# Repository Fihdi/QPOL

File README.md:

# 8hp Quad Pole Phaser

QPOL is an 8hp Eurorack phaser module with four voltage controllable all pass filters. A variety of frequency responses can be achieved by mixing the phase shifted output back to the input signal. Chaining multiple phaser modules together allows for phasing with 4, 8, 12, 16 etc poles.

# IN
Connect an audio signal to the **IN** jack. The input signal is internally mixed together to the output of the **FDBK** section. This mixed signal is then fed to the four all pass filters. The **IN** signal is also routed to the **OUT** jack where it is mixed together the filter output **P4** with variable strength.
# SHIFT
The **SHIFT** knob, **CV** jack, as well as its attenuverter knob, set the the cutoff frequency of the all pass filters. By modulating the **SHIFT** parameter, the filter changes the phase shift of the **IN**. An LED indicates the level of modulation.
# FDBK
The FDBK attenuverter controls the amount and polarity of feedback from the filter output **P4**, which is added back to the input signal. An external signal from the **EXT** input jack can be routed to the FDBK attenuverter with the **P4 EXT** switch.
# P4, OUT and MIX

The **P4** jack directly outputs the fourth stage of the all pass filter core. When chaining multiple modules together to allow for more than four stages of phasing, this output can be used

The **MIX** knob sums the **IN** signal to the filter output **P4** with variable strength. By changing the Jumper on the back of the module from "Direct" to "Mixed" a different input signal is fed to the MIX section. The jumper being in the "Direct" position routes the signal from the **IN** jack to the MIX section as it is. In the "Direct" position, the summed signal of the **IN** jack and the **FDBK** output is fed to the MIX section.

The final output is available at the **OUT** jack.

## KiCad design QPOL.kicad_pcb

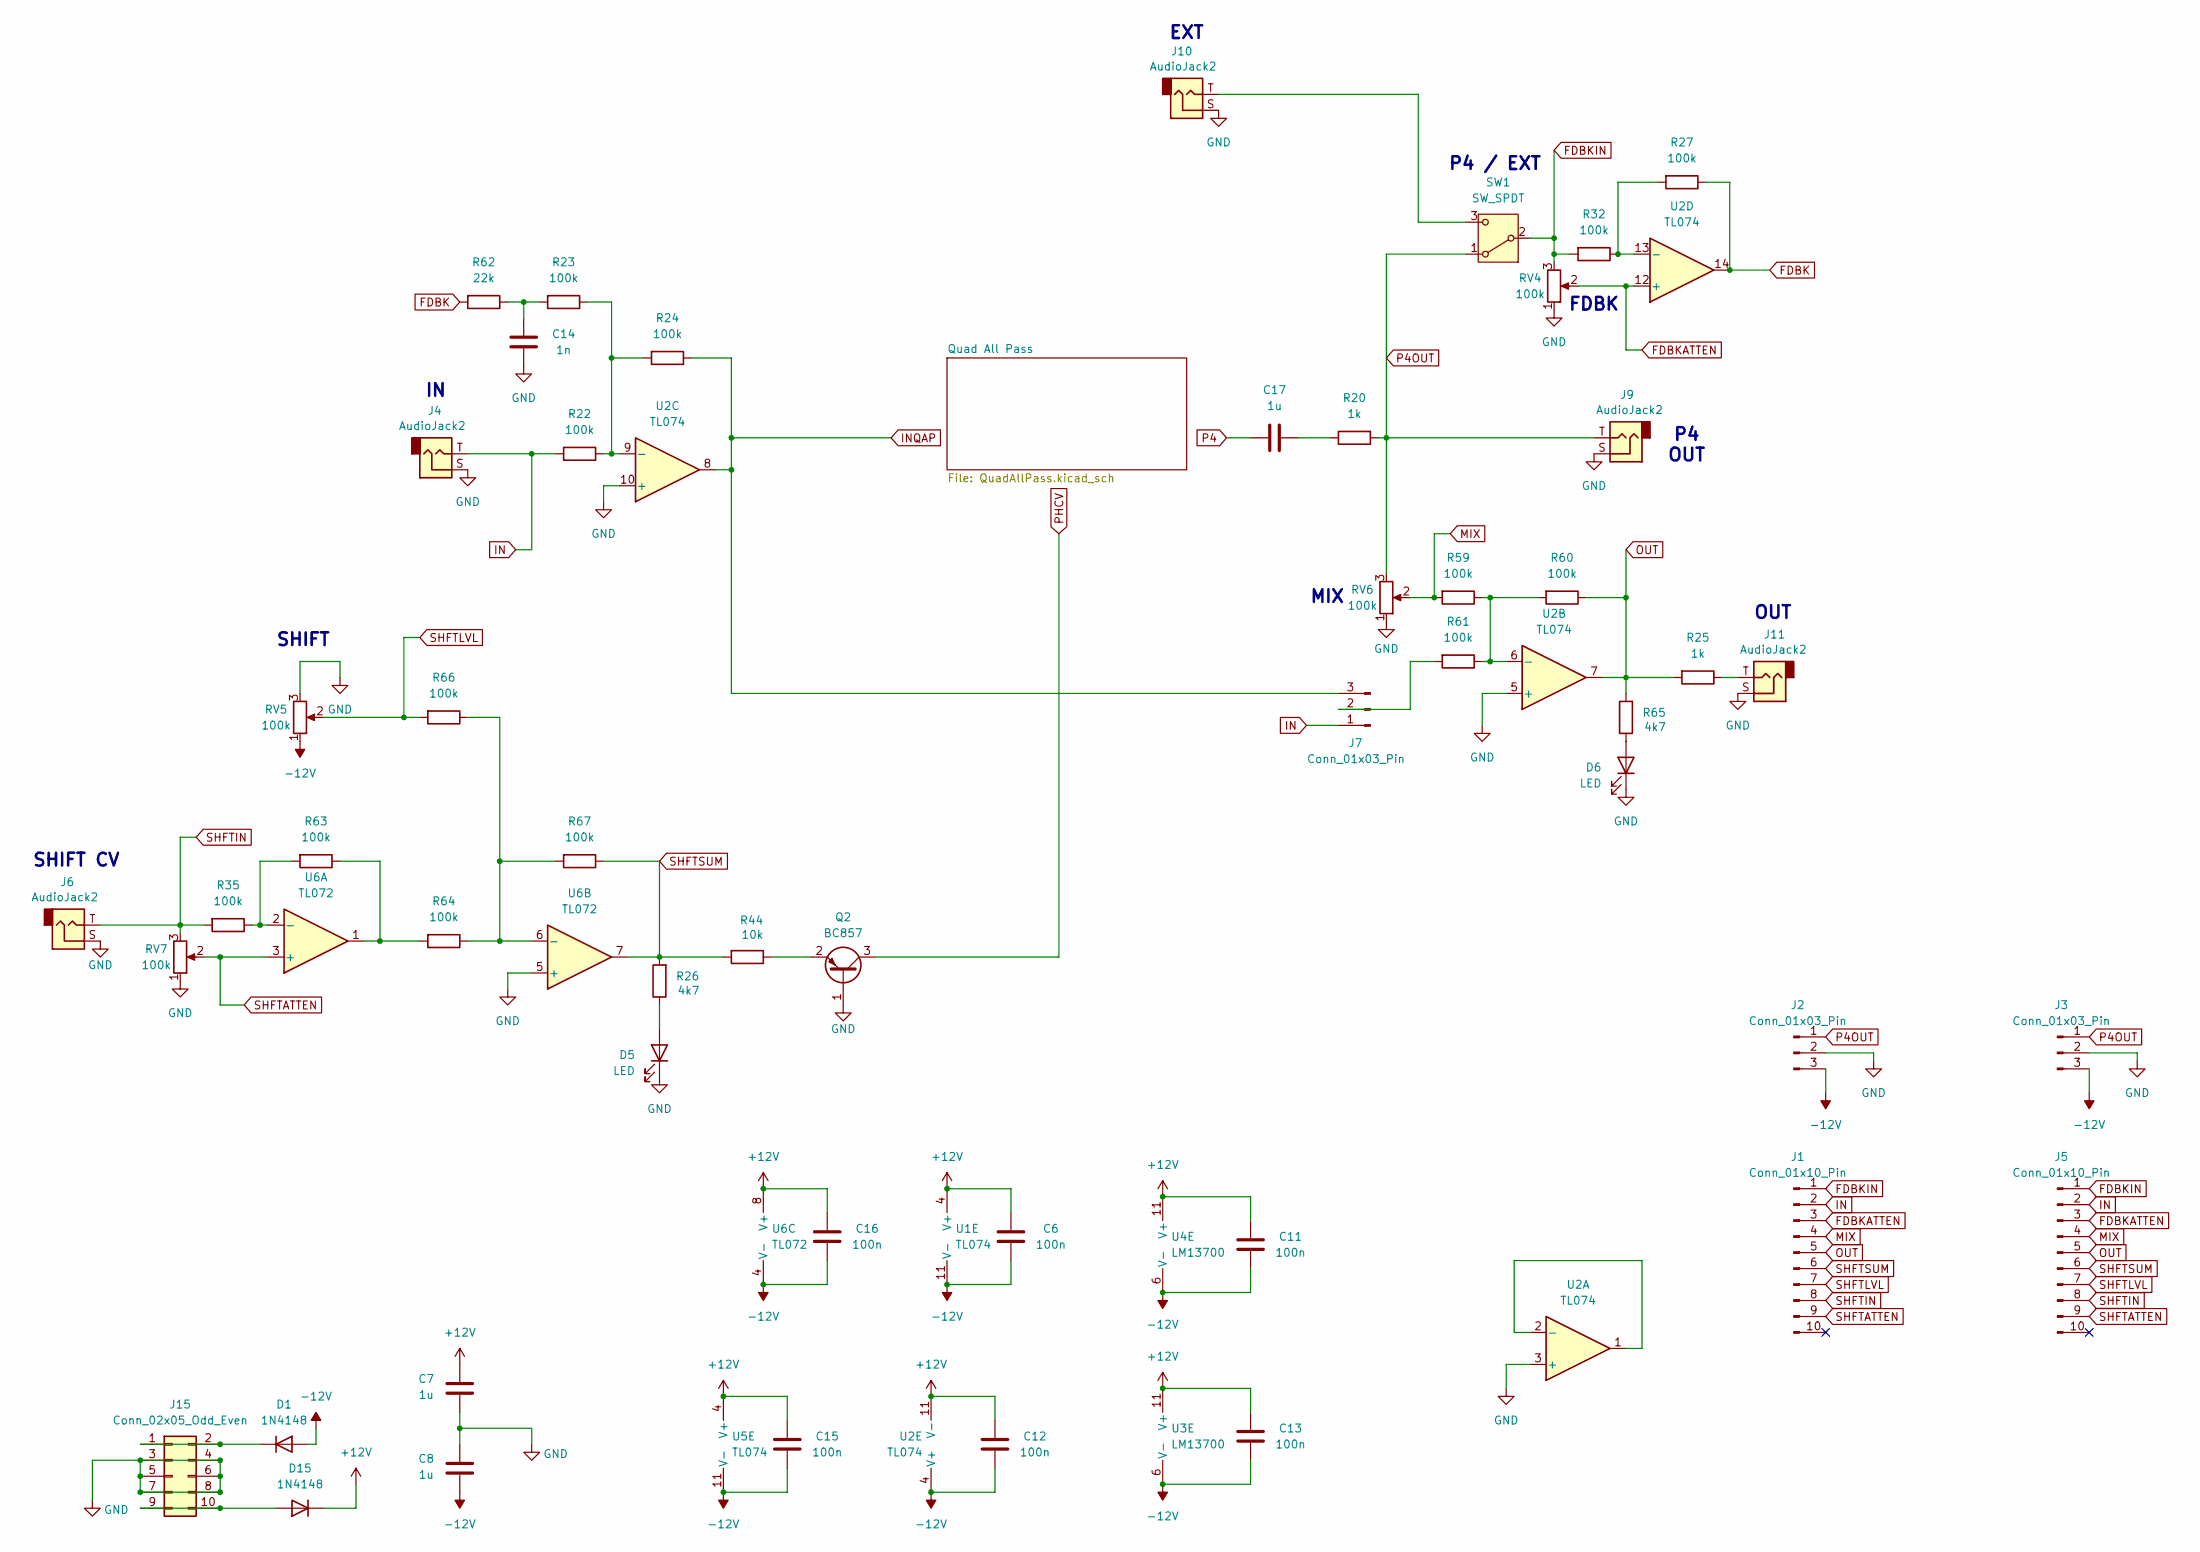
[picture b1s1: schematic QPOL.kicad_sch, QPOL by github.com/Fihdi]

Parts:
C6, C11, C12, C13, C15, C16: 100n; C_0805_2012Metric
C7, C8, C17: 1u; C_0805_2012Metric
C14: 1n; C_0805_2012Metric
D1, D15: 1N4148; D_SOD-323_HandSoldering
D5, D6: LED; LED_D3.0mm
J1, J5: Conn_01x10_Pin; PinHeader_1x10_P2.54mm_Vertical
J2, J3: Conn_01x03_Pin; PinHeader_1x03_P2.54mm_Vertical
J4, J6, J9, J10, J11: AudioJack2; MonoTRS
J7: Conn_01x03_Pin; PinSocket_1x03_P2.54mm_Vertical
J15: Conn_02x05_Odd_Even; IDC-Header_2x05_P2.54mm_Vertical
Q2: BC857; SOT-23
R20, R25: 1k; R_0805_2012Metric
R22, R23, R24, R27, R32, R35, R59, R60, R61, R63, R64, R66, R67: 100k; R_0805_2012Metric
R26, R65: 4k7; R_0805_2012Metric
R44: 10k; R_0805_2012Metric
R62: 22k; R_0805_2012Metric
RV4, RV5, RV6, RV7: 100k; Potentiometer_Alpha_RD901F-40-00D_Single_Vertical
SW1: SW_SPDT; Switch
U1, U2, U5: TL074; TSSOP-14_4.4x5mm_P0.65mm
U3, U4: LM13700; SOIC-16_3.9x9.9mm_P1.27mm
U6: TL072; SOIC-8_3.9x4.9mm_P1.27mm

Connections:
+12V: C6.1, C7.1, C11.1, C12.1, C13.1, C15.1, C16.1, D15.1 (K), U1.4 (V+), U2.11 (V-), U3.11 (V+), U4.11 (V+), U5.4 (V+), U6.8 (V+)
-12V: C6.2, C8.2, C11.2, C12.2, C13.2, C15.2, C16.2, D1.2 (A), J2.3, J3.3, RV5.1, U1.11 (V-), U2.4 (V+), U3.6 (V-), U4.6 (V-), U5.11 (V-), U6.4 (V-)
FDBK: R27.1, R62.2, U2.14
FDBKATTEN: J1.3, J5.3, RV4.2, U2.12 (+)
FDBKIN: J1.1, J5.1, R32.2, RV4.3, SW1.2 (B)
GND: C7.2, C8.1, C14.2, D5.1 (K), D6.1 (K), J2.2, J3.2, J4.S, J6.S, J9.S, J10.S, J11.S, J15.3, J15.4, J15.5, J15.6, J15.7, J15.8, Q2.1 (B), RV4.1, RV5.3, RV6.1, RV7.1, U2.3 (+), U2.5 (+), U2.10 (+), U6.5 (+); also elsewhere on the board
IN: J1.2, J4.T, J5.2, J7.1, R22.2
INQAP: J7.3, R24.1, U2.8; also elsewhere on the board
MIX: J1.4, J5.4, R59.2, RV6.2
unnamed: C14.1, R23.2, R62.1
unnamed: C17.2, R20.1
unnamed: D1.1 (K), J15.1, J15.2
unnamed: D5.2 (A), R26.1
unnamed: D6.2 (A), R65.1
unnamed: D15.2 (A), J15.9, J15.10
unnamed: J7.2, R61.2
unnamed: J11.T, R25.1
unnamed: Q2.2 (E), R44.1
unnamed: R63.1, R64.2, U6.1
unnamed: J10.T, SW1.3 (C)
unnamed: U2.1, U2.2 (-)
unnamed: R59.1, R60.2, R61.1, U2.6 (-)
unnamed: R22.1, R23.1, R24.2, U2.9 (-)
unnamed: R27.2, R32.1, U2.13 (-)
unnamed: R35.1, R63.2, U6.2 (-)
unnamed: R64.1, R66.1, R67.2, U6.6 (-)
OUT: J1.5, J5.5, R25.2, R60.1, R65.2, U2.7
P4: C17.1; also elsewhere on the board
P4OUT: J2.1, J3.1, J9.T, R20.2, RV6.3, SW1.1 (A)
PHCV: Q2.3 (C); also elsewhere on the board
SHFTATTEN: J1.9, J5.9, RV7.2, U6.3 (+)
SHFTIN: J1.8, J5.8, J6.T, R35.2, RV7.3
SHFTLVL: J1.7, J5.7, R66.2, RV5.2
SHFTSUM: J1.6, J5.6, R26.2, R44.2, R67.1, U6.7

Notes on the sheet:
OUT
FDBK
SHIFT
SHIFT CV
EXT
MIX
P4 OUT
P4 / EXT

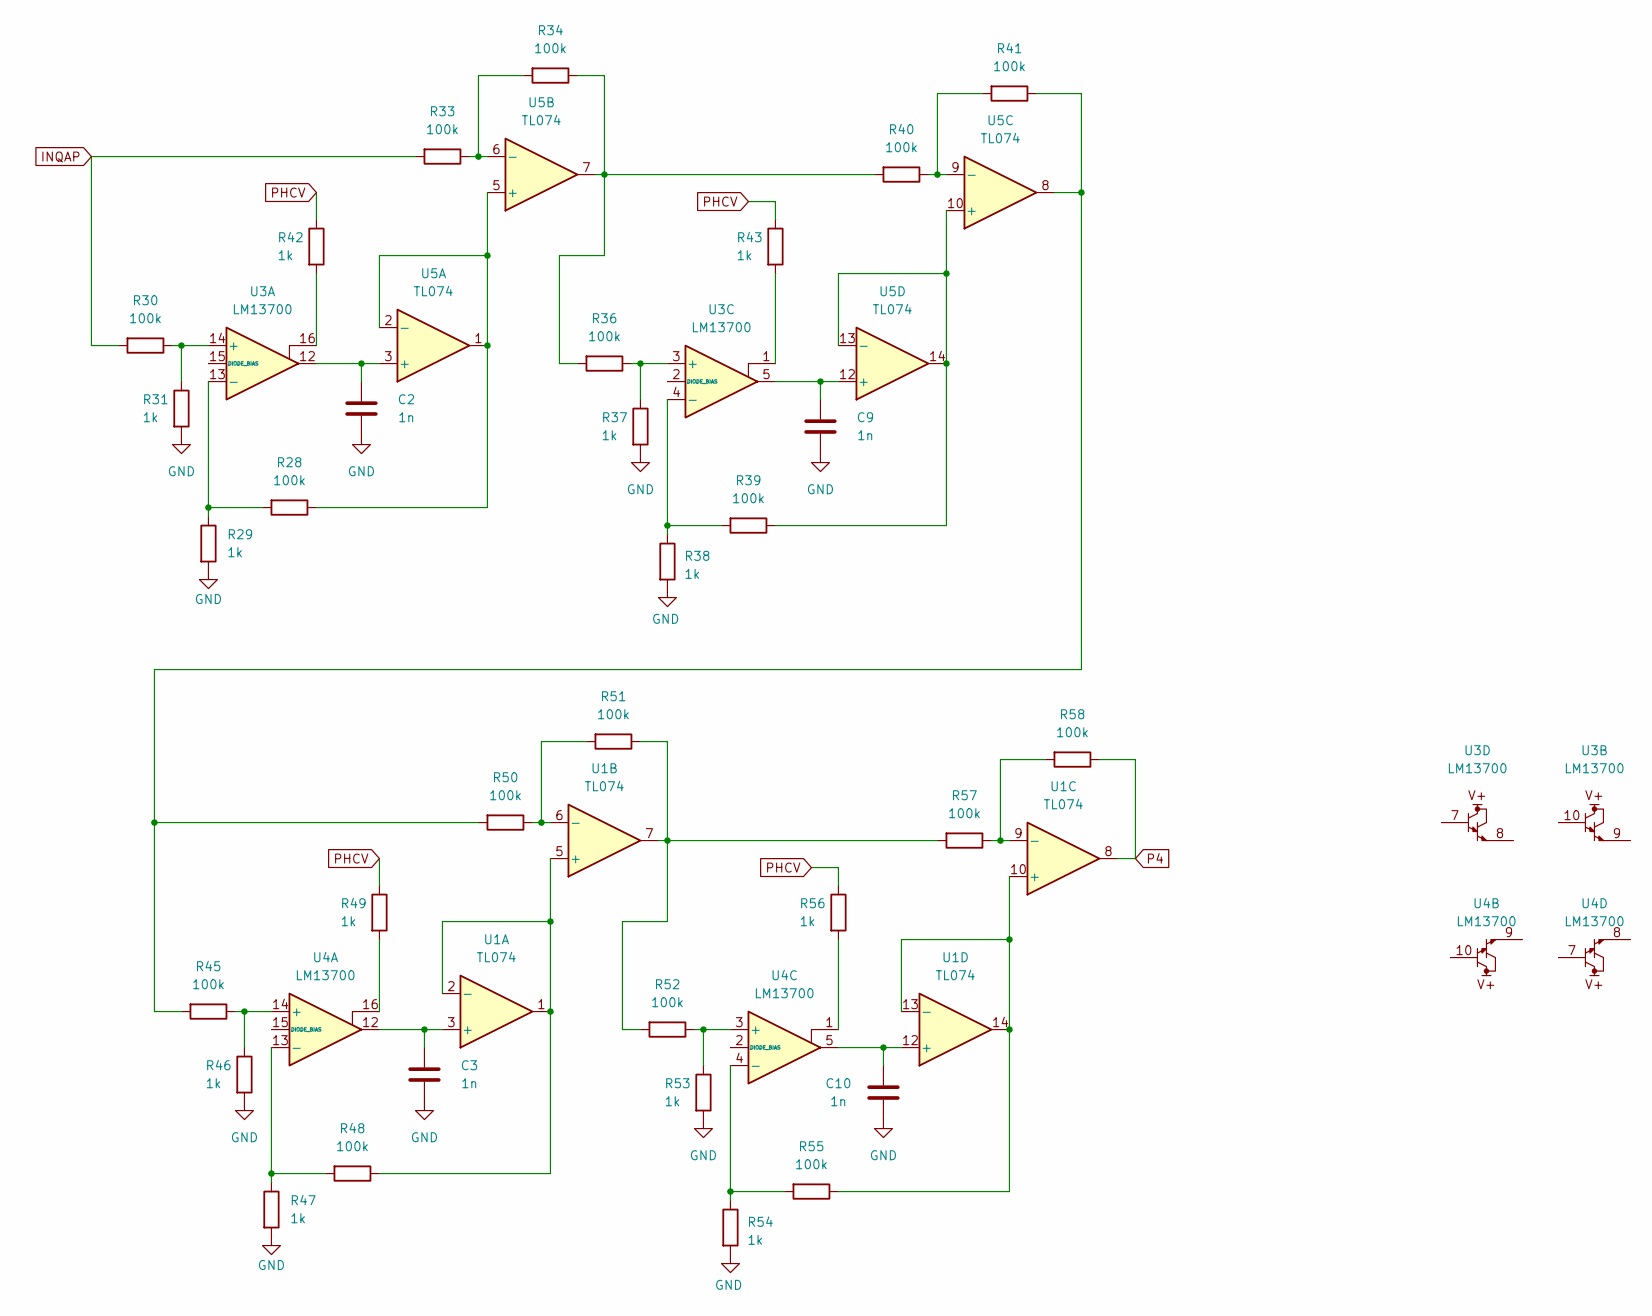
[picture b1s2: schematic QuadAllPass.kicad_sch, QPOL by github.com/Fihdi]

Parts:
C2, C3, C9, C10: 1n; C_0805_2012Metric
R28, R30, R33, R34, R36, R39, R40, R41, R45, R48, R50, R51, R52, R55, R57, R58: 100k; R_0805_2012Metric
R29, R31, R37, R38, R42, R43, R46, R47, R49, R53, R54, R56: 1k; R_0805_2012Metric
U1, U5: TL074; TSSOP-14_4.4x5mm_P0.65mm
U3, U4: LM13700; SOIC-16_3.9x9.9mm_P1.27mm

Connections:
GND: C2.2, C3.2, C9.2, C10.2, R29.2, R31.2, R37.2, R38.2, R46.2, R47.2, R53.2, R54.2; also elsewhere on the board
INQAP: R30.2, R33.2; also elsewhere on the board
unnamed: R34.1, R36.2, R40.2, U5.7
unnamed: R41.1, R45.2, R50.2, U5.8
unnamed: R42.2, U3.16
unnamed: R43.2, U3.1
unnamed: R49.2, U4.16
unnamed: R51.1, R52.2, R57.2, U1.7
unnamed: R56.2, U4.1
unnamed: C3.1, U1.3 (+), U4.12
unnamed: R48.1, U1.1, U1.2 (-), U1.5 (+)
unnamed: R50.1, R51.2, U1.6 (-)
unnamed: R55.1, U1.10 (+), U1.13 (-), U1.14
unnamed: R57.1, R58.2, U1.9 (-)
unnamed: C10.1, U1.12 (+), U4.5
unnamed: R30.1, R31.1, U3.14 (+)
unnamed: R28.2, R29.1, U3.13 (-)
unnamed: R36.1, R37.1, U3.3 (+)
unnamed: R38.1, R39.2, U3.4 (-)
unnamed: R45.1, R46.1, U4.14 (+)
unnamed: R47.1, R48.2, U4.13 (-)
unnamed: R52.1, R53.1, U4.3 (+)
unnamed: R54.1, R55.2, U4.4 (-)
unnamed: C2.1, U3.12, U5.3 (+)
unnamed: R28.1, U5.1, U5.2 (-), U5.5 (+)
unnamed: R33.1, R34.2, U5.6 (-)
unnamed: R39.1, U5.10 (+), U5.13 (-), U5.14
unnamed: R40.1, R41.2, U5.9 (-)
unnamed: C9.1, U3.5, U5.12 (+)
P4: R58.1, U1.8; also elsewhere on the board
PHCV: R42.1, R43.1, R49.1, R56.1; also elsewhere on the board

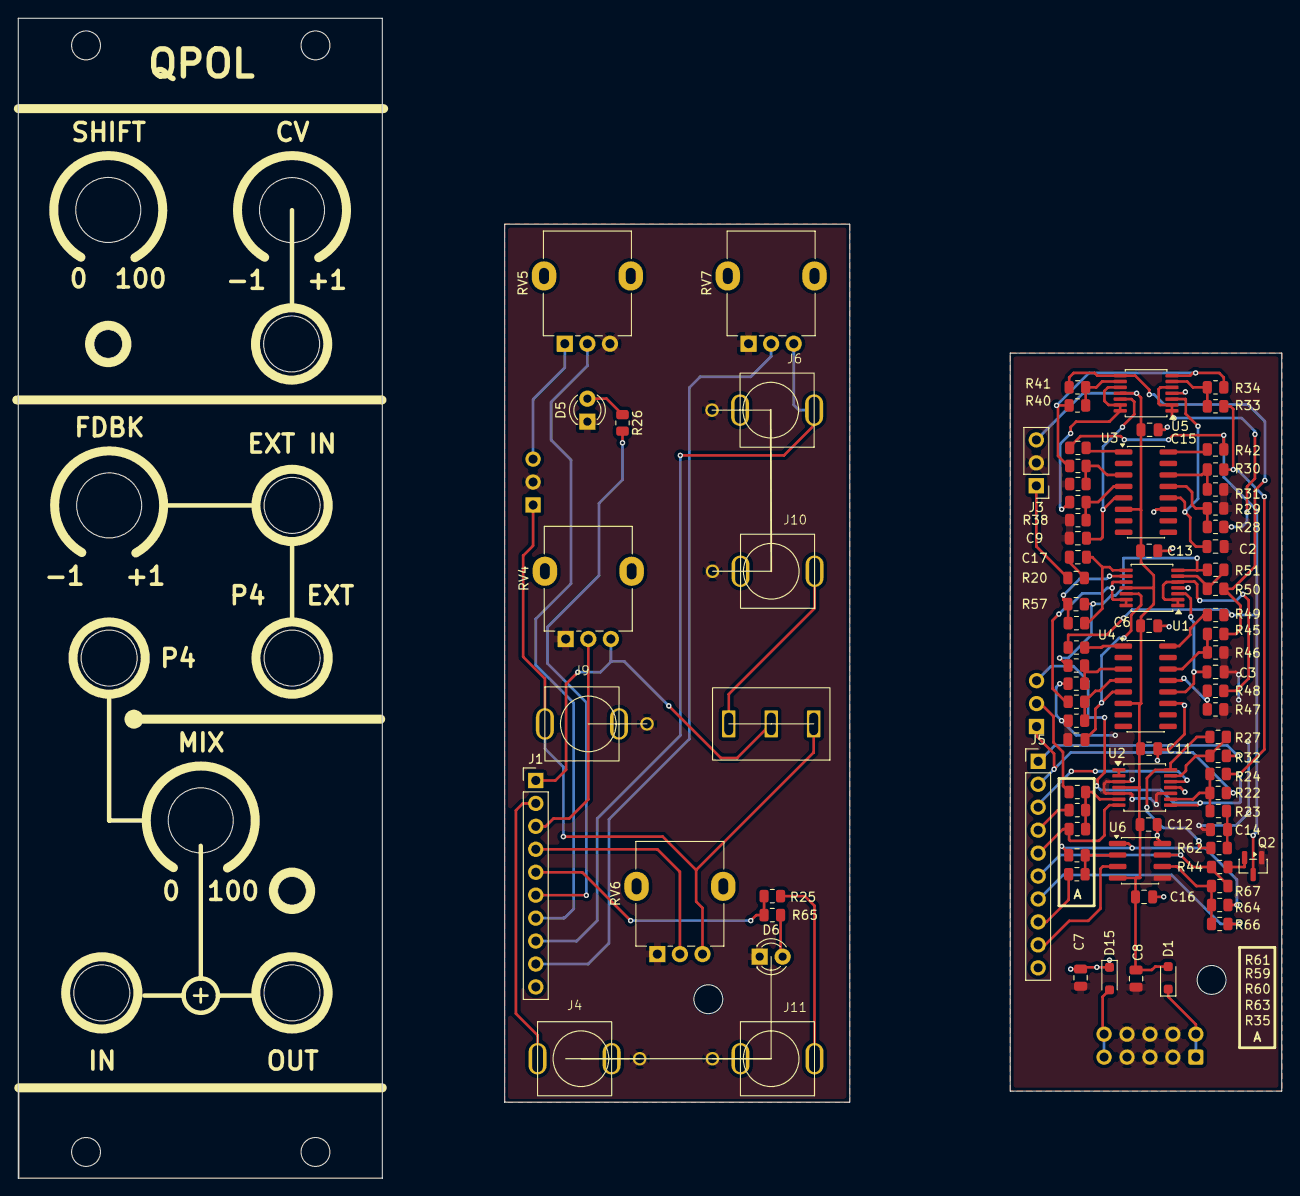
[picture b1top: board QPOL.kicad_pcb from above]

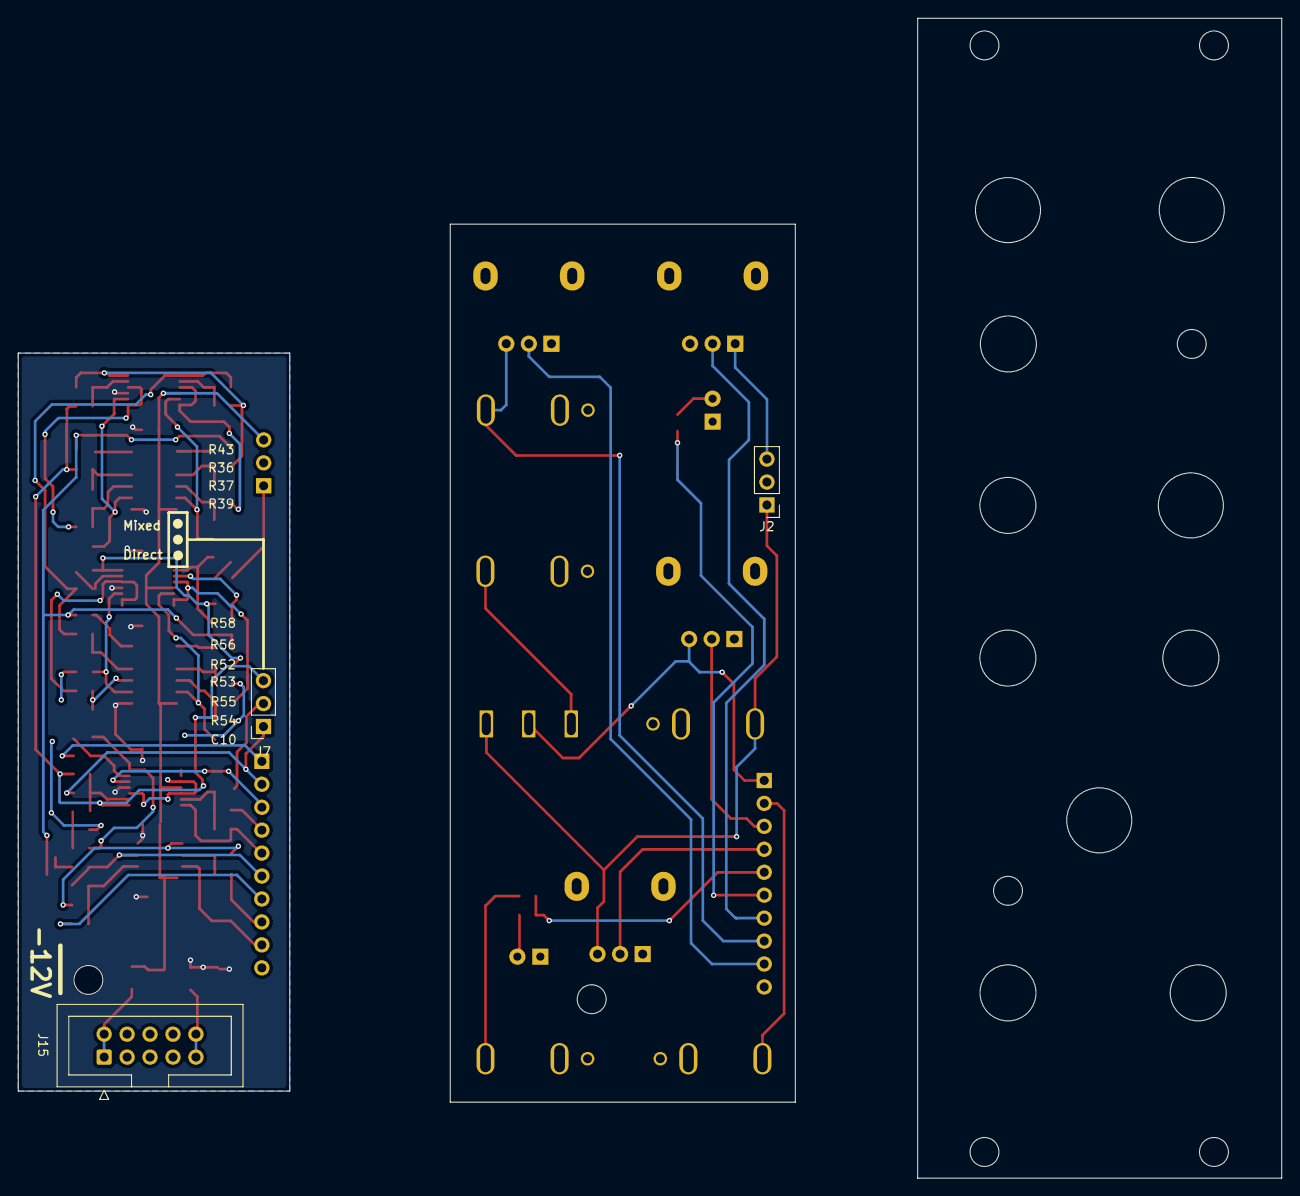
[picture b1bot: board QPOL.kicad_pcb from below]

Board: 2 copper layers, 30.1 x 81.7 mm, 88 parts (3 on the bottom side), 61 nets.

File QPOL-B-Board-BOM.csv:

"Reference","Qty","Value","Footprint"
"C2,C3,C9,C10,C14","5","1n","Capacitor_SMD:C_0805_2012Metric"
"C6,C11,C12,C13,C15,C16","6","100n","Capacitor_SMD:C_0805_2012Metric"
"C7,C8,C17","3","1u","Capacitor_SMD:C_0805_2012Metric"
"D1,D15","2","1N4148","Diode_SMD:D_SOD-323_HandSoldering"
"D5,D6","2","LED","LED_THT:LED_D3.0mm"
"J1,J5","2","Conn_01x10_Pin","Connector_PinHeader_2.54mm:PinHeader_1x10_P2.54mm_Vertical"
"J2,J3","2","Conn_01x03_Pin","Connector_PinHeader_2.54mm:PinHeader_1x03_P2.54mm_Vertical"
"J4,J6,J9,J10,J11","5","AudioJack2","Library:MonoTRS"
"J15","1","Conn_02x05_Odd_Even","Connector_IDC:IDC-Header_2x05_P2.54mm_Vertical"
"Q2","1","BC857","Package_TO_SOT_SMD:SOT-23"
"R20,R25,R29,R31,R37,R38,R42,R43,R46,R47,R49,R53,R54,R56","14","1k","Resistor_SMD:R_0805_2012Metric"
"R22,R23,R24,R27,R28,R30,R32,R33,R34,R35,R36,R39,R40,R41,R45,R48,R50,R51,R52,R55,R57,R58,R59,R60,R61,R63,R64,R66,R67","29","100k","Resistor_SMD:R_0805_2012Metric"
"R26,R65","2","4k7","Resistor_SMD:R_0805_2012Metric"
"R44","1","10k","Resistor_SMD:R_0805_2012Metric"
"R62","1","22k","Resistor_SMD:R_0805_2012Metric"
"RV4,RV5,RV6,RV7","4","100k","Potentiometer_THT:Potentiometer_Alpha_RD901F-40-00D_Single_Vertical"
"SW1","1","SW_SPDT","Library:Switch"
"U1,U2,U5","3","TL074","Package_SO:TSSOP-14_4.4x5mm_P0.65mm"
"U3,U4","2","LM13700","Package_SO:SOIC-16_3.9x9.9mm_P1.27mm"
"U6","1","TL072","Package_SO:SOIC-8_3.9x4.9mm_P1.27mm"
